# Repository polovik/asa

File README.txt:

Convenient utility for analyze TIFF file - AsTiffTagViewer: https://www.awaresystems.be/imaging/tiff/astifftagviewer.html

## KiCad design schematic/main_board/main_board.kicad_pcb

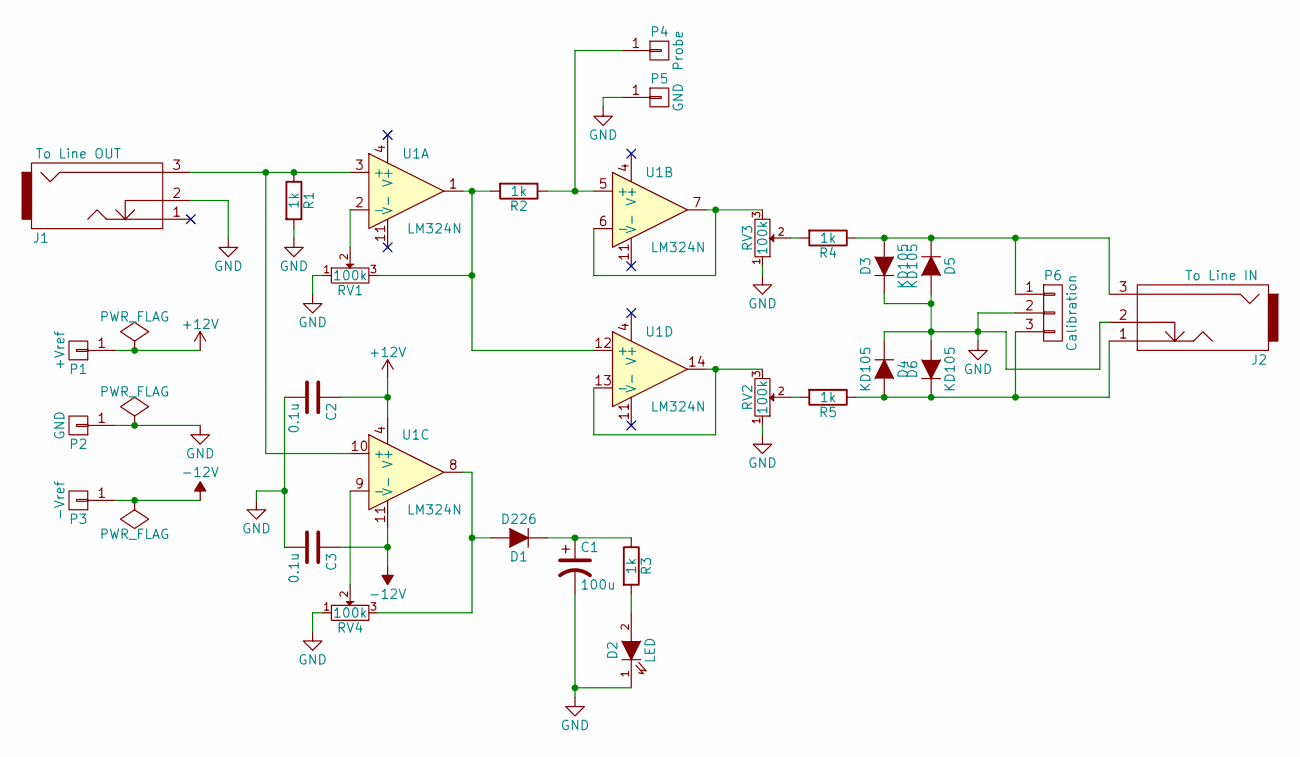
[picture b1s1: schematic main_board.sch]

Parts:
C1: 100u; C100u_vert
C2, C3: 0.1u; C_0.1u
D1: D226; Diode_D226
D2: LED; Pin_vert_1x02
D3, D4, D5, D6: KD105; Diode_KD105
J1: To Line OUT; PINHEAD1-3
J2: To Line IN; PINHEAD1-3
P1: +Vref; 1pin_small
P2, P5: GND; 1pin_small
P3: -Vref; 1pin_small
P4: Probe; 1pin_small
P6: Calibration; PINHEAD1-3
R1, R2, R3: 1k; Resistor_Horizontal_RM20mm_0.25W
R4, R5: 1k; Resistor_Horizontal_RM15mm
RV1, RV2, RV3, RV4: 100k; Potentiometer_CP3-36
U1: LM324N; DIP-14_W7.62mm_LongPads

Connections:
+12V: C2.1, P1.1, U1.4 (V+)
-12V: C3.1, P3.1, U1.11 (V-)
GND: C1.2, C2.2, C3.2, D2.1 (K), D3.1 (K), D4.1 (K), D5.2 (A), D6.2 (A), J1.2, J2.2, P2.1, P5.1, P6.2, R1.2, RV1.1, RV2.1, RV3.1, RV4.1
unnamed: C1.1, D1.1 (K), R3.1
unnamed: D1.2 (A), RV4.3, U1.8
unnamed: D2.2 (A), R3.2
unnamed: D3.2 (A), D5.1 (K), J2.3, P6.1, R4.1
unnamed: D4.2 (A), D6.1 (K), J2.1, P6.3, R5.1
unnamed: J1.3, R1.1, U1.3 (+), U1.10 (+)
unnamed: P4.1, R2.1, U1.5 (+)
unnamed: R2.2, RV1.3, U1.1, U1.12 (+)
unnamed: R4.2, RV3.2
unnamed: R5.2, RV2.2
unnamed: RV1.2, U1.2 (-)
unnamed: RV2.3, U1.13 (-), U1.14
unnamed: RV3.3, U1.6 (-), U1.7
unnamed: RV4.2, U1.9 (-)

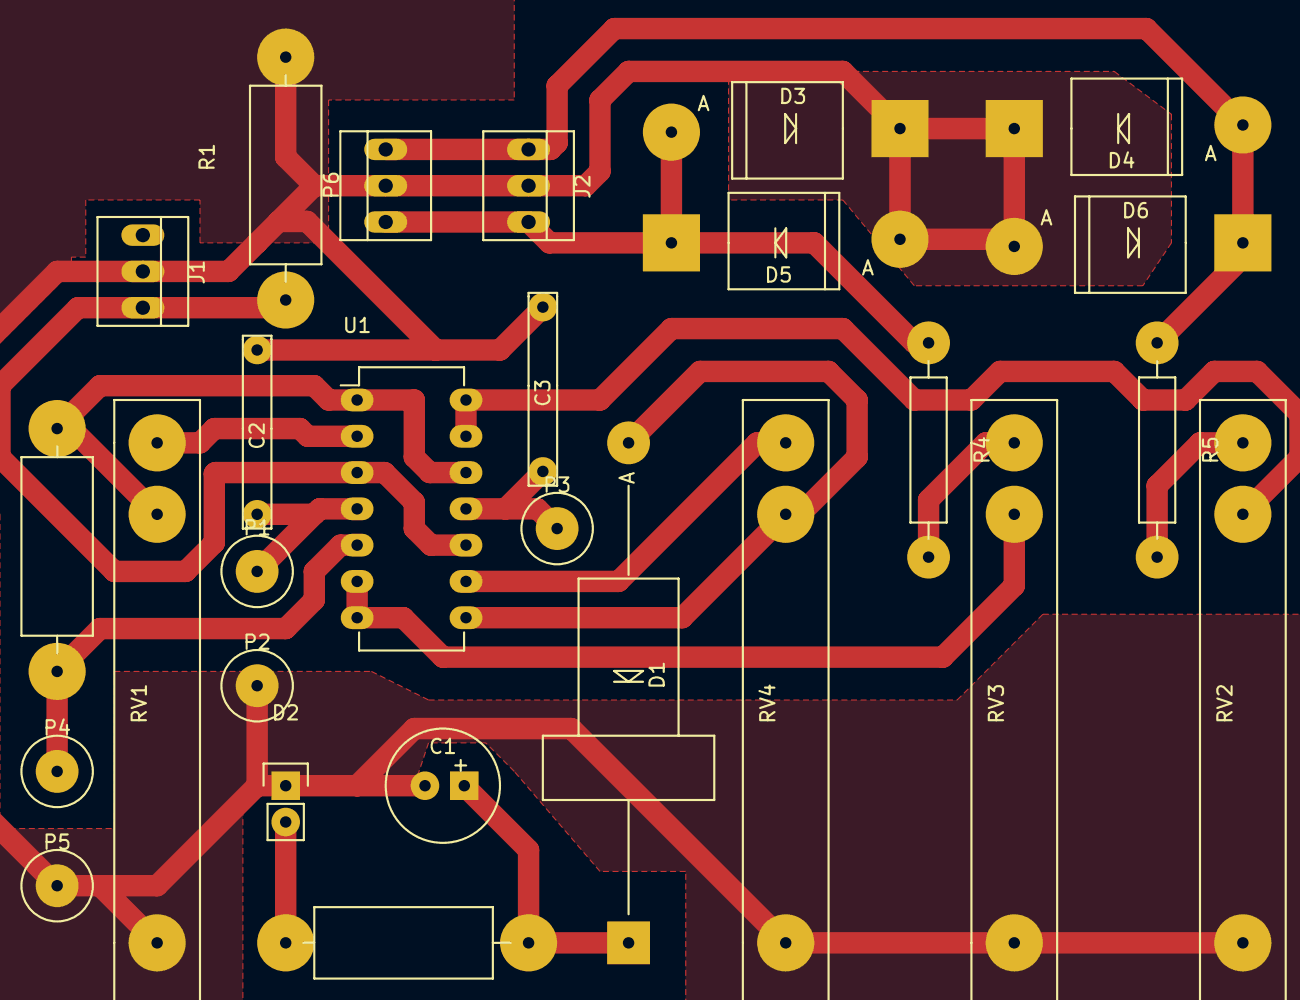
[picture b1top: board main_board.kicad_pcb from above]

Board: 2 copper layers, 27 parts (0 on the bottom side), 17 nets.

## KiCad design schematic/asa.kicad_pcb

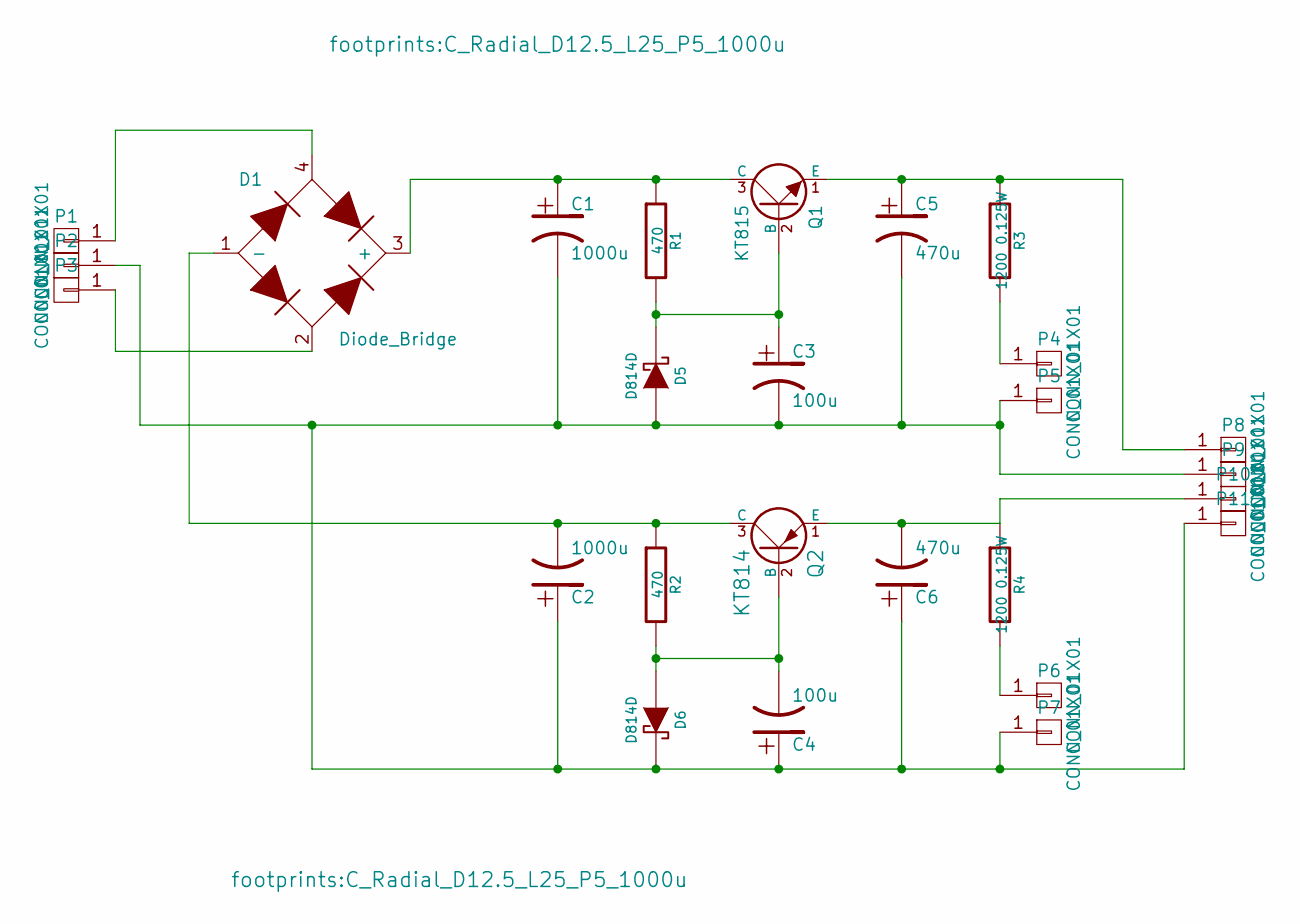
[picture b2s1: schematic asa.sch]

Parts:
C1, C2: 1000u; C_Radial_D12.5_L25_P5_1000u
C3, C4: 100u; C100u_horiz
C5, C6: 470u; C_Radial_D13_L21_P5_470u
D1: Diode_Bridge; Diode_Bridge_22x22
D5, D6: D814D; Diode_P600_Horizontal_D814
P1, P2, P3, P4, P5, P6, P7, P8, P9, P10, P11: CONN_01X01; 1pin_big
Q1: KT815; SOT126_SOT32_Housing_Vertical_KT81x
Q2: KT814; SOT126_SOT32_Housing_Vertical_KT81x
R1, R2: 470; Resistor_Horizontal_RM20mm_0.5W
R3, R4: 1200 0.125W; Resistor_Horizontal_RM20mm_0.25W

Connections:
unnamed: C1.1, D1.3 (+), Q1.3 (C), R1.1
unnamed: C1.2, C2.1, C3.2, C4.1, C5.2, C6.1, D5.1 (A), D6.2 (K), P2.1, P5.1, P7.1, P9.1, P11.1
unnamed: C2.2, D1.1 (-), Q2.3 (C), R2.1
unnamed: C3.1, D5.2 (K), Q1.2 (B), R1.2
unnamed: C4.2, D6.1 (A), Q2.2 (B), R2.2
unnamed: C5.1, P8.1, Q1.1 (E), R3.1
unnamed: C6.2, P10.1, Q2.1 (E), R4.1
unnamed: D1.2, P3.1
unnamed: D1.4, P1.1
unnamed: P4.1, R3.2
unnamed: P6.1, R4.2

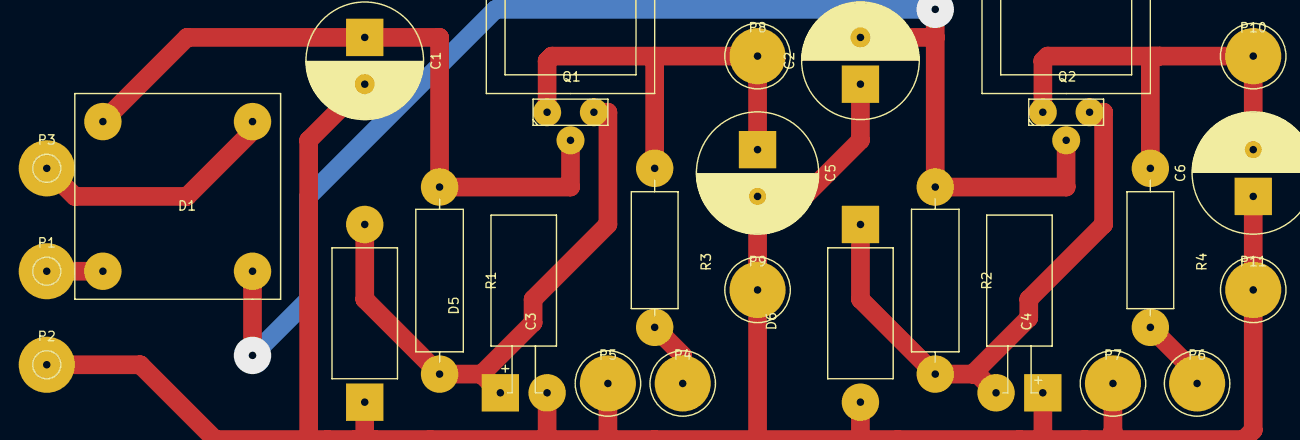
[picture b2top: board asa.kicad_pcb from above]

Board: 2 copper layers, 26 parts (0 on the bottom side), 11 nets.

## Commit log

2016-07-12 Sin 441Hz is generated.
2016-07-14 Add sources of QCustomPlot 1.3.2 from http://www.qcustomplot.com/index.php/download
2016-07-14 Realise audio capture.
2016-07-14 QCustomPlot is integrated in GUI.
2016-07-15 Correct audio capture - start/stop at any time. Fix sin tone generation.
2016-07-15 Remove audiocapture.
2016-07-15 Start/stop Tone generator at any time.
2016-07-15 Change frequency on-the-fly. Enumerate, display and switch audio output devices.
2016-07-15 Enumerate audio input devices.
2016-07-15 Switch audio input on-the-fly.
2016-07-18 Add Auto and Normal trigger to UI.
2016-07-19 Describe deploying procedure on Windows. Add logging to file.
2016-07-19 Apply layouts to GUI.
2016-07-21 Capture from both channels.
2016-07-21 Flexible tone generation.
2016-07-22 Switch output tone's waveform.
2016-07-22 Add icons to Trigger Slope. Start capture with none channel.
2016-07-22 Implement Single trigger mode.
2016-07-22 Add icons for buttons Play and Capture.
2016-07-22 Fixed "Empty list of audio devices on Windows"
2016-07-27 Track only one channel in Normal or Single trigger mode.
2016-07-30 Change the MainWindow - for switch between separate forms.
2016-07-31 Form "Diagnose" is added.
2016-07-31 Fix photo grabbing. Added placeholder for display photos.
2016-08-02 License's type is specified.
2016-08-04 Photo fit to view on start. Photo may be zoomed and dragged.
2016-08-04 Show context menu for add, remove testpoint, view entire photo. Redraw testpoints upon zooming.
2016-08-04 Testpoint is selectable and movable. Each testpoint has ID.
2016-08-04 Display selected testpoint by animation. Display testpoint's ID.
2016-08-05 Testpoints can't be moved outside the photo. Display already existed testpoints upon photo loading.
2016-08-05 Added sources of libtiff library and some parts of Qt's plugin for TIFF support. Sources are obtained from Qt-5.7.0 source code.
2016-08-05 Added sources of zlib library. Sources are obtained from Qt-5.7.0 source code.
2016-08-05 Create class ImageTiff. Tiff image writing is implemented.
2016-08-07 Add possibility to store multiple custom tags.
2016-08-10 Added Power Supply schematic.
2016-08-10 Add procedure for store multiple images in one TIFF file.
2016-08-10 Reenumerate rest of testpoints upon a testpoint removing. Add placeholder for SAVE procedure.
2016-08-10 Created widget SignarureView. Store original board photo and with markers to the TIFF file.
2016-08-11 Looking after testpoints' actions on BoardView in FormDiagnose.
2016-08-13 Import Tiff file READ procedure.
2016-08-13 Read custom tags from multipage TIFF file.
2016-08-13 Store and read a signature raw data in TIFF file.
2016-08-14 Trace route the schematic on PCB 170x52mm.
2016-08-14 Reduce PCB size to 140x52mm.
2016-08-22 Change PCB boarders.
2016-08-22 Added Form Analyze.
2016-08-22 Tie sliders and spinboxes on form Analyze.
2016-08-22 Move Audio device selection to Calibration form. Stop audio devices when form is leaved. Added audio device controlling to th Analyze form.
2016-08-23 Play tone on separate channels during calibration. Lock signature on form Analyze.
2016-08-23 Display level of input voltage separately for each channel.
2016-08-24 Added schematic for the main board.
2016-08-24 Add possibility to generate and setup maximal voltage amplitude for ToneGenerator.
2016-08-24 Change amplitude volume for ToneGenerator.
2016-08-25 Added class for store/restore settings in INI file.
2016-08-25 Add class for convenient utilise ToneWaveForm types.
2016-08-25 Store a signature and photo using ImageTiff class.
2016-08-25 Open single signature file in form Analyze.
2016-08-26 Display hints on form Calibration.
2016-08-26 Trace route some wires on PCB.
2016-08-26 Make project's files structure more intuitive.
2016-08-26 Reformat code style.
2016-08-29 Add footprint for potentiometer.
2016-08-29 Configure maximum voltage on all forms.
2016-08-29 Added application's logo icon.
2016-08-30 Added circuit to schematic for limit output voltage range.
2016-08-30 Added precompiled ZLib library for Windows32. Downloaded from http://zlib.net/zlib128-dll.zip
2016-08-30 Fix deploying on Windows platform. Add launcher for Linux.
2016-08-31 Fix voltage amplitude following max value.
2016-08-31 Added footprints for some soviet elements which used on Main board.
2016-08-31 For avoid recursion, stop processing signal "valueChanged" until UI boxes are updated.
2016-08-31 Remove unused code from audioinputdevice.
2016-08-31 Added possibility to change application's language.
2016-09-01 Added 0.1u capacitors and filled zones to PCB.
2016-09-01 Added russian translations.
2016-09-01 Make Form Calibration flexible.
2016-09-01 Added form "About".
2016-09-05 Move logic about ID manipulation from BoardView to the FormDiagnose.
2016-09-05 Unite UI items for run calibration.
2016-09-05 Update help for the button Calibrate.
2016-09-05 Added icons to tab buttons.
2016-09-05 Added sources of FancyTabBar from https://github.com/benadler/FancyTabBar at commit 2c86ca974104980b5a8a35ff331588999cca7a12.
2016-09-06 Use FancyTabBar instead of leftPanel in MainWindow.
2016-09-06 Save testpoints in ascending order.
2016-09-06 Added stuff for make deb-package.
2016-09-07 Do not put files after building into Build directory on Linux - change pro-file for correct Deb-package creation.
2016-09-07 Fix build's dependent stuff.
2016-09-07 Automate preparing sources for OSC.
2016-09-07 Fix Ubuntu 14.04 building - use Qt 5.2.1 API when work with Web-camera.
2016-09-08 Add spec file for build RPM packages.
2016-09-08 Fix package building for OpenSuse.
2016-09-09 Use system libs for Linux - zlib and tiff instead of building ourself.
2016-09-09 Build tiff library separately.
2016-09-11 Added appveyor.yml
2016-09-11 Move libtiff and zlib to separate repository - 3rd-party.
2016-09-11 Build dependencies at first.
2016-09-11 Exit from 3rd folder.
2016-09-11 Fix 3rd build folder.
2016-09-11 Fix deploy QTDIR
2016-09-11 Zip deployed files.
2016-09-11 Fix appveyor
2016-09-11 Fix zip archive name.
2016-09-11 Try to fix web-camera detection.
2016-09-12 Use Qt's tool for collect required Qt's libraries and plugins. Inform user when some lib from 3rd-party folder is missed.
2016-10-03 Fix #1 - Flush output buffers when ToneGenerator starts.
2016-10-03 Move data processing for oscilloscope to separate class - OscilloscopeEngine (Issue #2).
2016-10-04 Done #3 - replace SignatureView with OscilloscopeView in form Calibration.
2016-10-04 Fix #10 - Increasing RMS Voltage leads to decreasing it's value - form Calibraion.
2016-10-05 Display human-frendly names for audio sources on Linux (from pulseaudio). Issue #7
2016-10-05 Display human-frendly names for audio sinks on Linux (from pulseaudio). Issue #7
2016-10-05 Display human-frendly names for audio sources and sinks on Windows (from DirectSound). Issue #7
2016-10-07 Fixed #11 - Sound card STLab CM106 is invalid configured after plugging to PC. By default, LineIn or Mic port is muted. It needs to play with PulseAudio and Alsamixer to unmute it correctly.
2016-10-08 Closed #13 - Display on form Calibration data from audio input irrelative to the Generator's tone amplitude.
2016-10-08 Closed #2 - Change amplify factor and samples' offsets for audio input device.
2016-10-22 Close #14 - Reduce debug output for non-verbose mode.
2016-10-22 Fixed #6 - Volume level indicator isn't refreshed upon the window resizing.
2016-10-22 Close #9 - By default zoom only time axis. For zoom level axis it needs to additionally press any modifier key on keyboard.
2016-10-23 Closed #16 - Add icons for buttons on forms Calibrate and Analyze.
2016-10-23 Closed #15 (Decrease range of input channel offsets but increase step of offsets). Fixed #8 - enable/disable widgets on Calibration form depending on Calibrate button state.
2016-10-24 Simplify schematic for post on wiki.
2016-10-25 Add image which displays block diagram of the schematic circut.
2016-10-25 Add labels to jack connectors.
2016-11-02 Close #5 - use global settings for configure audio capture device volume on Linux.
2016-11-07 Close #4 - Adjust global audio capture volume level on Windows Vista+. Used EndpointVolume API, IAudioEndpointVolume interface, IMMDevice interface.
2016-11-08 Issue #22 - Display input signal's scope - added horizontal lines on form Calibration. Hide values under mouse and time measure lines on the form.
2016-11-08 Closed #22 - Zoom Signature view according to Uprobe.
2016-11-09 Revert input channels on form Analyze. Display nicer a signature.
2016-11-11 Issue #17 - screenshot of calibration procedure.
2016-11-11 Issue #17. Mark GUI components on screenshots.
2016-11-13 Fixed #23 - added missed translations.
2016-11-23 Display probe signal parameters on stored signatures. Fix voltage saving.
2016-11-25 Arrange items on form Diagnose.
2021-01-14 Fix building with Visual Studio MSVC compiler.
2021-01-17 Select first available audio device if no-one can be choose. Fix UID generation - MSVC rand() generate values lower than 0x7FFF. Enlarge board's view on form Diagnose.
2021-01-18 Add slider for software amplification of input signal to form Calibration. Update AppVeyor configuration.
2021-01-18 Control software amplification of input audio signal.
2021-01-18 Increase compilation verbosity. Fix compiler errors.
2021-01-19 Increase calculation of font size to fit rect for testpoint.
2021-01-20 Control UI mode switching on form Diagnose.
2021-01-20 Enable/disable some testpoint actions depends on selected Diagnose mode.
2021-01-20 Divide "Lock signature" button on two different - Show/hide previous signature and Hold signature.
2021-01-25 Divide Lock button on Diagnose form.
2021-01-25 Load testpoints' settings and save captured signatures on Diagnostic tab.
2021-01-27 Load any images as board's photo. Save photo from camera to PNG file.
